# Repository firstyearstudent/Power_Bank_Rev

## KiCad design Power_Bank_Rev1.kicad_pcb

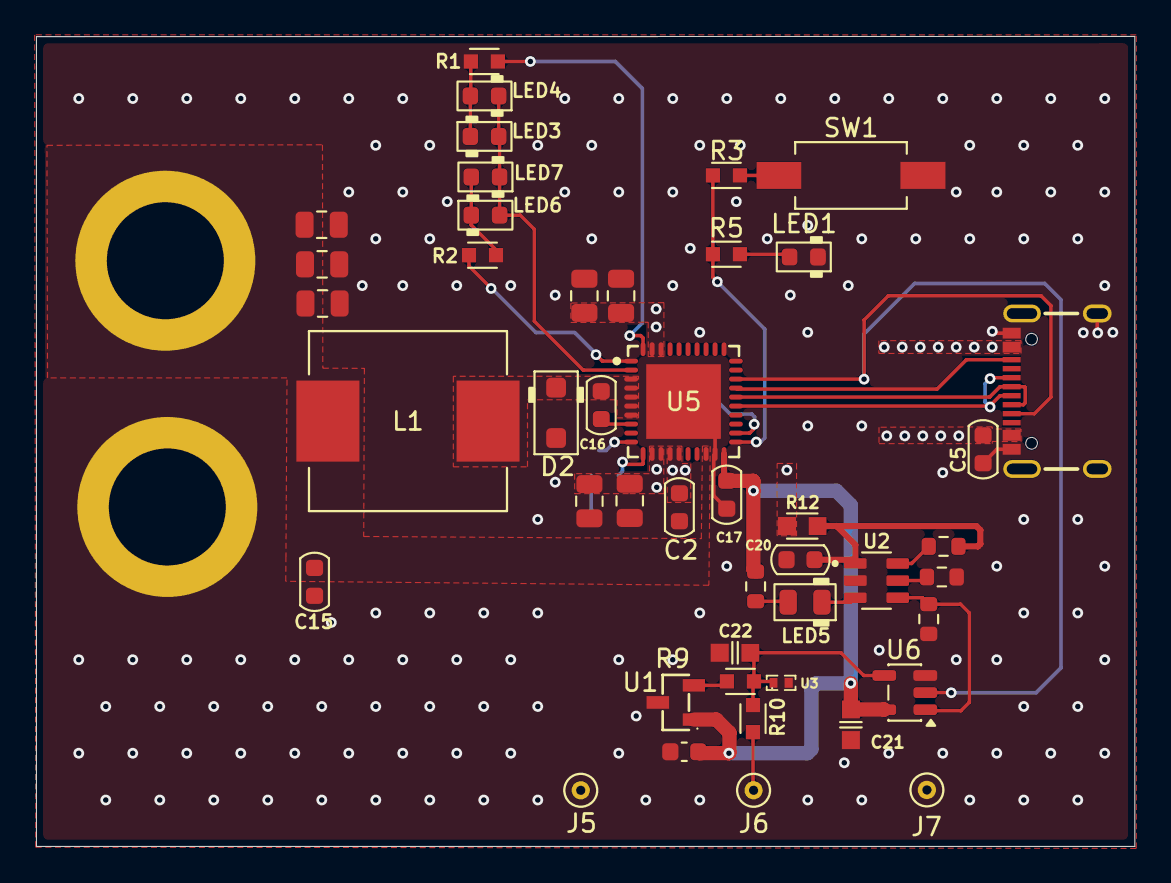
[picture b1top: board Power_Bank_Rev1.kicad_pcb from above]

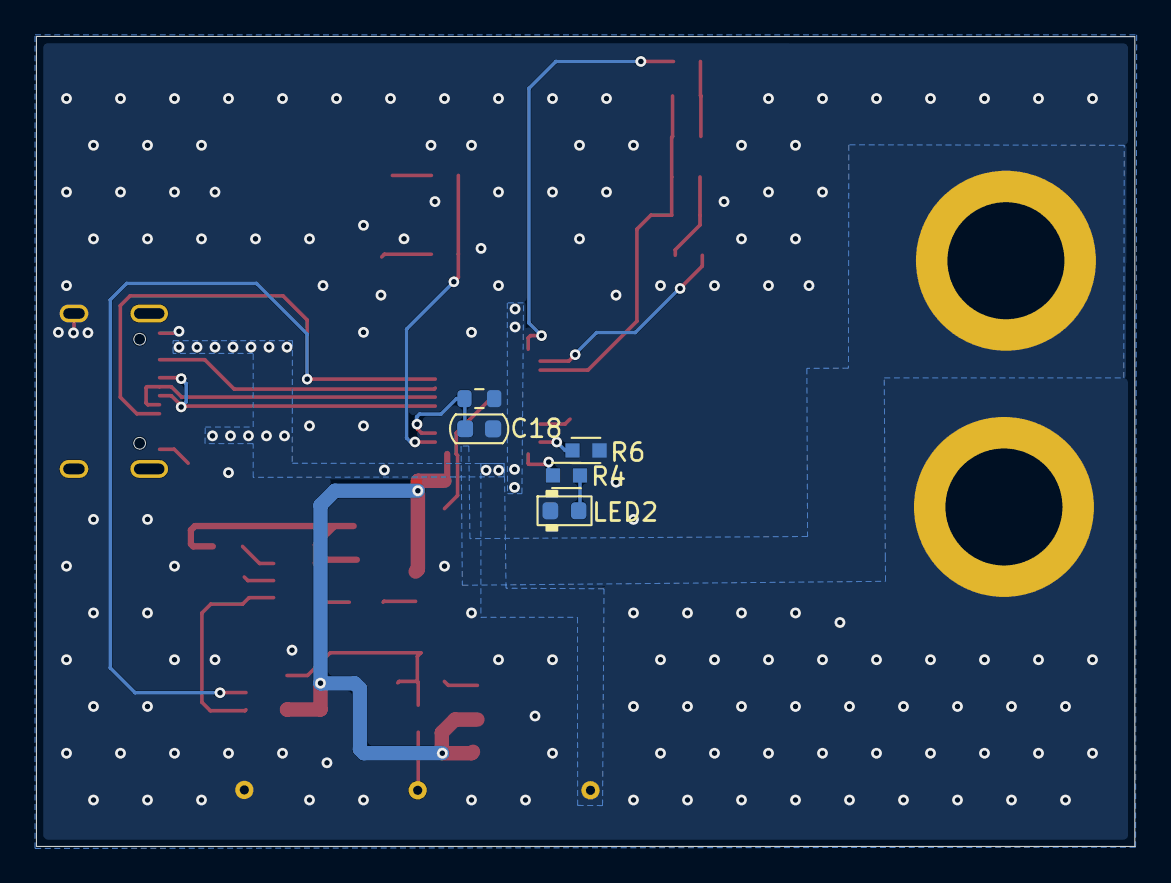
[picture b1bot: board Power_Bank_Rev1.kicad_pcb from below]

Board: 2 copper layers, 61.0 x 45.0 mm, 52 parts (5 on the bottom side), 32 nets.

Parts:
C2, C17: 2.2uF_0603; C_0603_1608Metric
C5, C15, C16, C18: 100nF_0603; C_0603_1608Metric
C8, C9, C10, C11, C12, C13, C14: 22uF; C_0805_2012Metric
C19: 0.1uF; C_0603_1608Metric
C20: 1uF_0603; C_0603_1608Metric
C21: 0.1uF_0603_16V; C_0603
C22: 10nF_0603_25V; C_0603
D2: PMEG4020ER; D_SOD-123F
J1: USB_C_Receptacle; USB-C_16
J3, J4: Conn_01x01; 1x01_6.5mm
J5, J6, J7: Pogo_Pin; MILL-MAX_0906-1-15-20-75-14-11-0
L1: 2.2uH; IND_F1F3-1004T-2R2M
LED1, LED2: LED_0603_Red; LED_0603_1608Metric
LED3: 100%; LED_0603_1608Metric
LED4: 75%; LED_0603_1608Metric
LED5: 100%; LED_0805_2012Metric
LED6: 50%; LED_0603_1608Metric
LED7: 25%; LED_0603_1608Metric
R1, R2, R4: 100R_0603; R_0603
R3: 10k_0603; R_0603
R5: 20R_0603; R_0603
R6, R10: 22k_0603; R_0603
R7, R11: 5.1k_DNI; R_0603_1608Metric
R8: 10k; R_0603_1608Metric
R9: 150k_0603; R_0603
R12: 1k_0603; R_0603
R13: 47k; R_0603_1608Metric
R14: 1k; R_0603_1608Metric
SW1: Switch_Tactile_CnK; Button_CnK_PTS636.0_6x3.5mm
U1: TMAG5231A2DQDBZR; SOT-23-3_L2.9-W1.3-P1.90-LS2.4-BL-1
U2: CH221K; SOT95P280X120-6N
U3: ESD5451N; DFN1006-2L-BI
U5: IP5356; VQFN-40_L6.0-W6.0-P0.50-TL-EP4.2
U6: TS5A3166DBVR; SOT-23-5

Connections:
/BAT: C8.1, C9.1, C14.1, C15.1, J3.1 (Pin_1_1), L1.2, U5.18 (BAT)
/CC1: J1.A5 (CC1), U5.28 (CC1), U6.2
/CC2: J1.B5 (CC2), U5.27 (CC2)
/DMC: J1.A7 (D-), J1.B7 (D-), U5.26 (DMC)
/DPC: J1.A6 (D+), J1.B6 (D+), U5.25 (DPC)
/IN: C22.1, R9.2, R10.2, U3.1, U6.4
/VCC: C17.1, C19.2, C21.1, R14.2, U1.1 (VCC), U5.20 (VCC), U6.5 (V+)
/VDD: C2.1, C5.1, J1.VBUS, J5.1 (1_1), R12.2, U5.14 (VBUS), U5.15 (VBUS)
/VSYS: C10.1, C11.1, C12.1, C13.1, U5.12 (VSYS), U5.13 (VSYS), U5.38 (VSYS), U5.39 (VSYS)
/WATER_DETECT: J6.1 (1_1), R10.1
GND: C2.2, C5.2, C8.2, C9.2, C10.2, C11.2, C12.2, C13.2, C14.2, C15.2, C17.2, C18.2, C19.1, C20.2, C21.2, C22.2, D2.2 (A), J1.GND, J1.S (SHIELD), J4.1 (Pin_1_1), J7.1 (1_1), LED1.1 (K), LED2.1 (K), R6.2, R7.1, R8.2, R11.1, SW1.2, U1.3 (GND), U2.2 (GND), U3.2, U5.19 (AGND), U5.41 (EPAD), U6.3 (GND)
unnamed: C16.2, D2.1 (K), L1.1, U5.3 (LX), U5.4 (LX), U5.5 (LX), U5.6 (LX), U5.7 (LX)
unnamed: LED1.2 (A), R5.1
unnamed: LED2.2 (A), R4.2
unnamed: LED3.2 (A), LED4.1 (K), LED6.2 (A), LED7.1 (K), U5.2 (LED3)
unnamed: LED3.1 (K), LED4.2 (A), R1.2
unnamed: LED5.2 (A), R14.1
unnamed: LED5.1 (K), U2.3 (~PG)
unnamed: LED6.1 (K), LED7.2 (A), R2.2
unnamed: R3.2, SW1.1
unnamed: R9.1, U1.2 (OUT)
unnamed: R7.2, U2.4 (CC1), U6.1
unnamed: R11.2, U2.5 (CC2)
unnamed: R13.1, U2.6 (CFG)
unnamed: C20.1, R12.1, R13.2, U2.1 (VDD)
unnamed: C16.1, U5.8 (BST)
unnamed: R3.1, R5.2, U5.21 (KEY)
unnamed: R1.1, U5.40 (LED1)
unnamed: R2.1, U5.1 (LED2)
unnamed: R6.1, U5.10 (LED5)
unnamed: R4.1, U5.11 (LED6)
unnamed: C18.1, R8.1, U5.22 (NTC)
